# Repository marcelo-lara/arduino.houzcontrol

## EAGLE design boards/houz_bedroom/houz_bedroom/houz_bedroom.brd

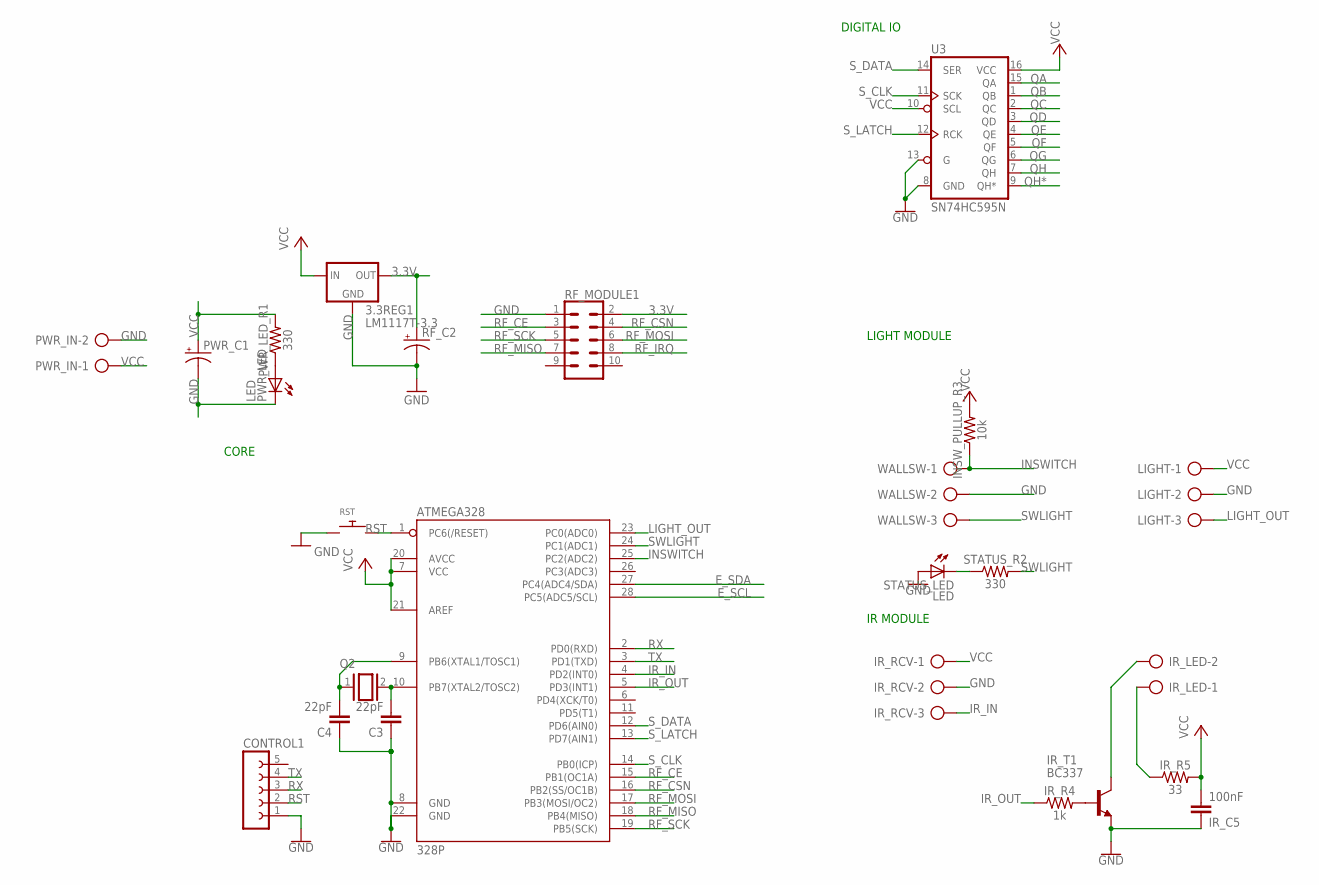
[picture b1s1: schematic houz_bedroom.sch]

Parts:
3.3REG1: LM1117T-3.3; TO220
ATMEGA328: 328P; DIP28
C3, C4: 22pF; C050-030X075
CONTROL1: FE05-1
INSW_PULLUP_R3: 10k; AXIAL-0.3
IR_C5: 100nF; C050-030X075
IR_LED: AK500/2-H
IR_R4: 1k; AXIAL-0.3
IR_R5: 33; AXIAL-0.3
IR_RCV: AK500/3
IR_T1: BC337; TO92
LIGHT: AK500/3
PWR_C1: CPOL-USE7.5-16; E7,5-16
PWR_IN: AK500/2-H
PWR_LED: LED; LED3MM
PWR_LED_R1: 330; AXIAL-0.3
Q2: 16MHz; QS
RF_C2: CPOL-USE5-10.5; E5-10,5
RF_MODULE1: CONN_05X2NO_SILK; 2X5_NOSILK
RST: SWITCH_PUSHBUTTONEVQ-PE; TACT_PANA-EVQ
STATUS_LED: LED; LED3MM
STATUS_R2: 330; AXIAL-0.3
U3: SN74HC595N; DIP16
WALLSW: AK500/3

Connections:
3.3V: 3.3REG1.2 (OUT), RF_C2.+, RF_MODULE1.2
E_SCL: ATMEGA328.28 (PC5(ADC5/SCL))
E_SDA: ATMEGA328.27 (PC4(ADC4/SDA))
GND: 3.3REG1.1 (GND), ATMEGA328.8 (GND), ATMEGA328.22 (GND), C3.1, C4.1, CONTROL1.1, IR_C5.1, IR_RCV.2, IR_T1.1 (E), LIGHT.2, PWR_C1.-, PWR_IN.2, PWR_LED.K (C), RF_C2.-, RF_MODULE1.1, RST.P$1, STATUS_LED.A, U3.8 (GND), U3.13 (G), WALLSW.2
INSWITCH: ATMEGA328.25 (PC2(ADC2)), INSW_PULLUP_R3.P$1 (1), WALLSW.1
IR_IN: ATMEGA328.4 (PD2(INT0)), IR_RCV.3
IR_LED1: IR_LED.1, IR_R5.P$1 (1)
IR_LED2: IR_LED.2, IR_T1.3 (C)
IR_OUT: ATMEGA328.5 (PD3(INT1)), IR_R4.P$1 (1)
IR_T1_B: IR_R4.P$2 (2), IR_T1.2 (B)
LIGHT_OUT: ATMEGA328.23 (PC0(ADC0)), LIGHT.3
unnamed: PWR_LED.A, PWR_LED_R1.P$1 (1)
QA: U3.15 (QA)
QB: U3.1 (QB)
QC: U3.2 (QC)
QD: U3.3 (QD)
QE: U3.4 (QE)
QF: U3.5 (QF)
QG: U3.6 (QG)
QH: U3.7 (QH)
QH*: U3.9 (QH*)
RF_CE: ATMEGA328.15 (PB1(OC1A)), RF_MODULE1.3
RF_CSN: ATMEGA328.16 (PB2(SS/OC1B)), RF_MODULE1.4
RF_IRQ: RF_MODULE1.8
RF_MISO: ATMEGA328.18 (PB4(MISO)), RF_MODULE1.7
RF_MOSI: ATMEGA328.17 (PB3(MOSI/OC2)), RF_MODULE1.6
RF_SCK: ATMEGA328.19 (PB5(SCK)), RF_MODULE1.5
RST: ATMEGA328.1 (PC6(/RESET)), CONTROL1.2, RST.P$2
RX: ATMEGA328.2 (PD0(RXD)), CONTROL1.3
ST_R2: STATUS_LED.K (C), STATUS_R2.P$1 (1)
SWLIGHT: ATMEGA328.24 (PC1(ADC1)), STATUS_R2.P$2 (2), WALLSW.3
S_CLK: ATMEGA328.14 (PB0(ICP)), U3.11 (SCK)
S_DATA: ATMEGA328.12 (PD6(AIN0)), U3.14 (SER)
S_LATCH: ATMEGA328.13 (PD7(AIN1)), U3.12 (RCK)
TX: ATMEGA328.3 (PD1(TXD)), CONTROL1.4
VCC: 3.3REG1.3 (IN), ATMEGA328.7 (VCC), ATMEGA328.20 (AVCC), ATMEGA328.21 (AREF), INSW_PULLUP_R3.P$2 (2), IR_C5.2, IR_R5.P$2 (2), IR_RCV.1, LIGHT.1, PWR_C1.+, PWR_IN.1, PWR_LED_R1.P$2 (2), U3.10 (SCL), U3.16 (VCC)
X3: ATMEGA328.9 (PB6(XTAL1/TOSC1)), C4.2, Q2.1
X4: ATMEGA328.10 (PB7(XTAL2/TOSC2)), C3.2, Q2.2

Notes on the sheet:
IR MODULE
LIGHT MODULE
CORE
DIGITAL IO

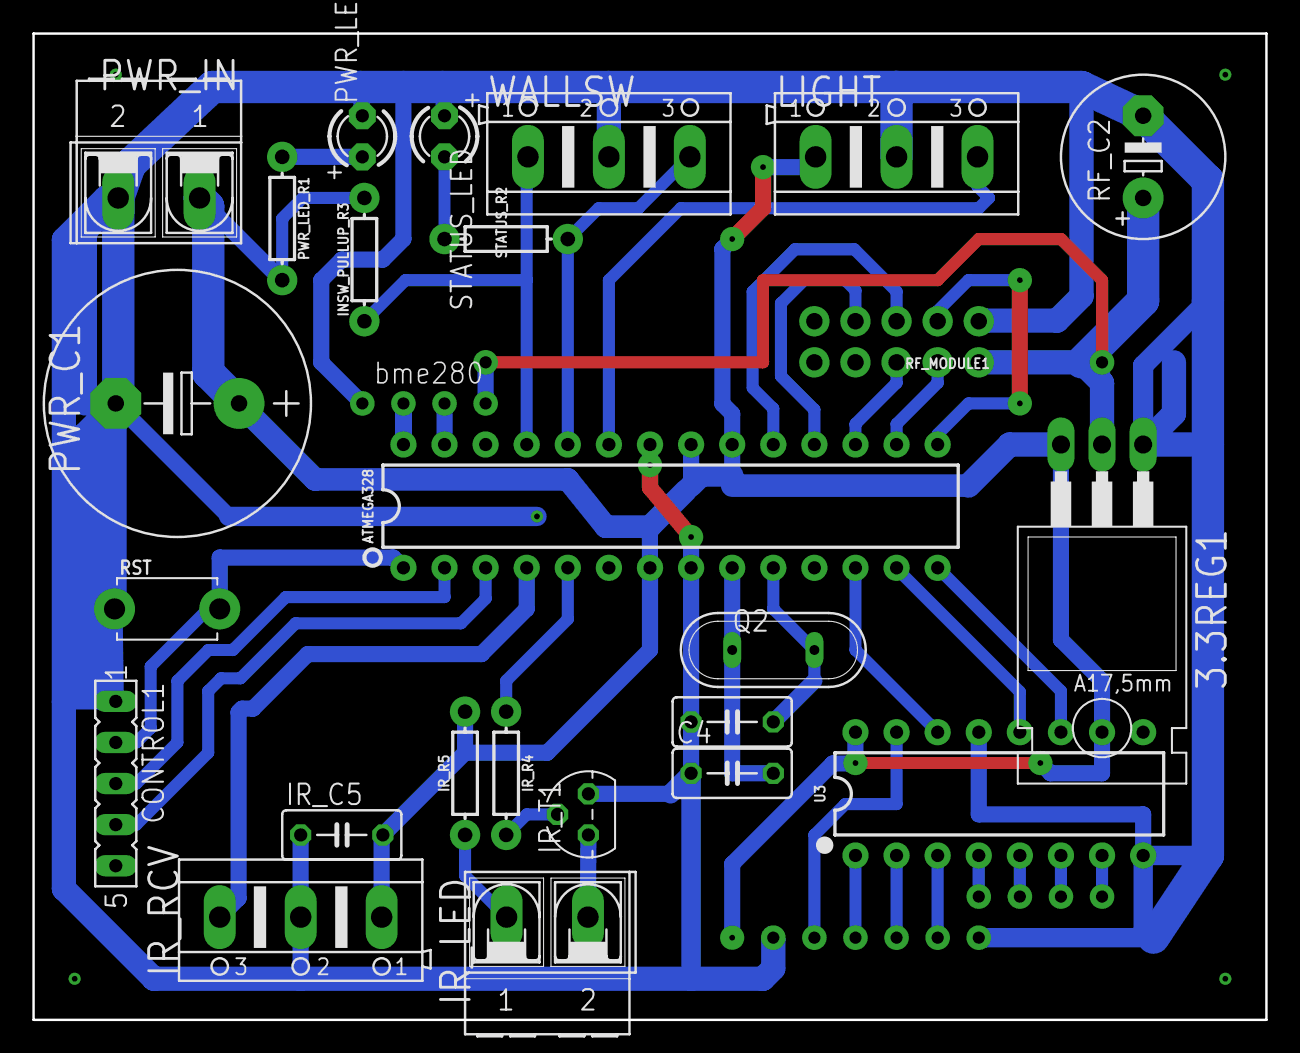
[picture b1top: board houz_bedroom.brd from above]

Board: 2 copper layers, 76.2 x 61.0 mm, 25 parts (0 on the bottom side), 26 nets.

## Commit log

2018-11-25 release_24NOV18
2018-12-01 add IRremote
2018-12-01 board config
2018-12-01 houzkeep definitions
2018-12-01 houz housekeep + refactor
2018-12-01 remove unused declarations
2018-12-01 rename office.ino to houze_office.ino
2018-12-01 fix encoding issue
2018-12-01 add comments
2018-12-02 IR add surrey commands
2018-12-02 add IR module
2018-12-02 ir lib customizations
2018-12-02 ignore vscode settings
2018-12-02 pragma once + devices refactor
2018-12-02 pushdata helper
2018-12-02 living switch to handler
2018-12-30 eagle: bedroom board design
2019-01-26 arduino back
2019-01-26 library rename
2019-01-26 vs config
2019-01-30 bedroom v2 setup
2019-01-31 pwm status led on pin 11 (D5)
2019-02-01 remove unused headers
2019-02-01 tab after drop
2019-02-01 light bugfix
2019-02-01 add IRLremote library
2019-02-03 wroking status
2019-02-03 add sonyIR codes for 38kHz
2019-02-03 update dallas
2019-02-03 add BME280 library
2019-02-03 bedroom bme280 reference
2019-02-03 bme280 weather ok
2019-02-04 introduce HouzWeather
2019-02-05 set retries to 9
2019-02-05 refactor suite devices
2019-02-05 event based handling
2019-02-05 status update
2019-02-06 console fix spaces
2019-02-06 wip changes
2019-02-07 wip weather tx
2019-02-12 enviroment pressureEncode
2019-02-12 enviroment device refactor
2019-02-12 statusLed anim
2019-03-23 webapp: nodejs server initial commit
2019-03-24 WIP: webapp
2019-03-24 wip: all ok prior to docker
2019-03-25 wip: webapp handle fan
2019-03-31 living: fixture ok
2019-03-31 pre production
2019-04-01 living: switch module
2019-04-07 fx: scenes introduction b0.1
2019-04-10 server: variable refactor
2019-04-10 houz: memory/timing optimization
2019-04-10 webapp: cleanup
2019-04-10 houz: inSwitchSetup
2019-04-11 suite: scene management
2019-04-11 refactor: bedroom>suite
2019-04-11 houz: statusled performance
2019-04-11 suite: ir scene handling
2019-04-11 houz: housekeep
2019-04-12 server: report status to host
2019-04-12 webapp: handle server status
2019-04-14 webapp: server debug status
2019-04-15 webapp: dicroRow enhancement
2019-04-16 houz: rf power > high
2019-04-16 webapp: fixed port change
2019-04-16 webapp: ui refactor
2019-04-16 webapp: ui iphone fix
2019-04-16 webapp: move bind to external js
2019-04-16 webapp: bind bugfixes
2019-04-16 webapp: move render outside main
2019-04-16 webapp: housekeep
2019-04-17 scene handling v1
2019-04-19 performance improvements
2019-04-22 suite: fan implementation bugfix
2019-04-22 houz: switch noise adjust
2019-04-22 office: upgrade (weather,switch,scenes)
2019-04-22 suite: fan output enhance
2019-04-22 webapp: fix duplicate binding
2019-04-24 dockerized webapp
2019-05-06 dmx slave board
2019-05-06 remove old pocs
2019-05-06 houz_office: update to v1.2
2019-05-06 remove old references
2019-05-11 libraries housekeep
2019-07-27 add wemos dummy node
2019-07-27 add raspi migration tool
2019-07-28 change wemos>dummy
2019-07-28 move rf configuration to it's own file

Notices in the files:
parts and their libraries:
SparkFun-Resistors: Licensing: Creative Commons ShareAlike 4.0 International - https://creativecommons.org/licenses/by-sa/4.0
